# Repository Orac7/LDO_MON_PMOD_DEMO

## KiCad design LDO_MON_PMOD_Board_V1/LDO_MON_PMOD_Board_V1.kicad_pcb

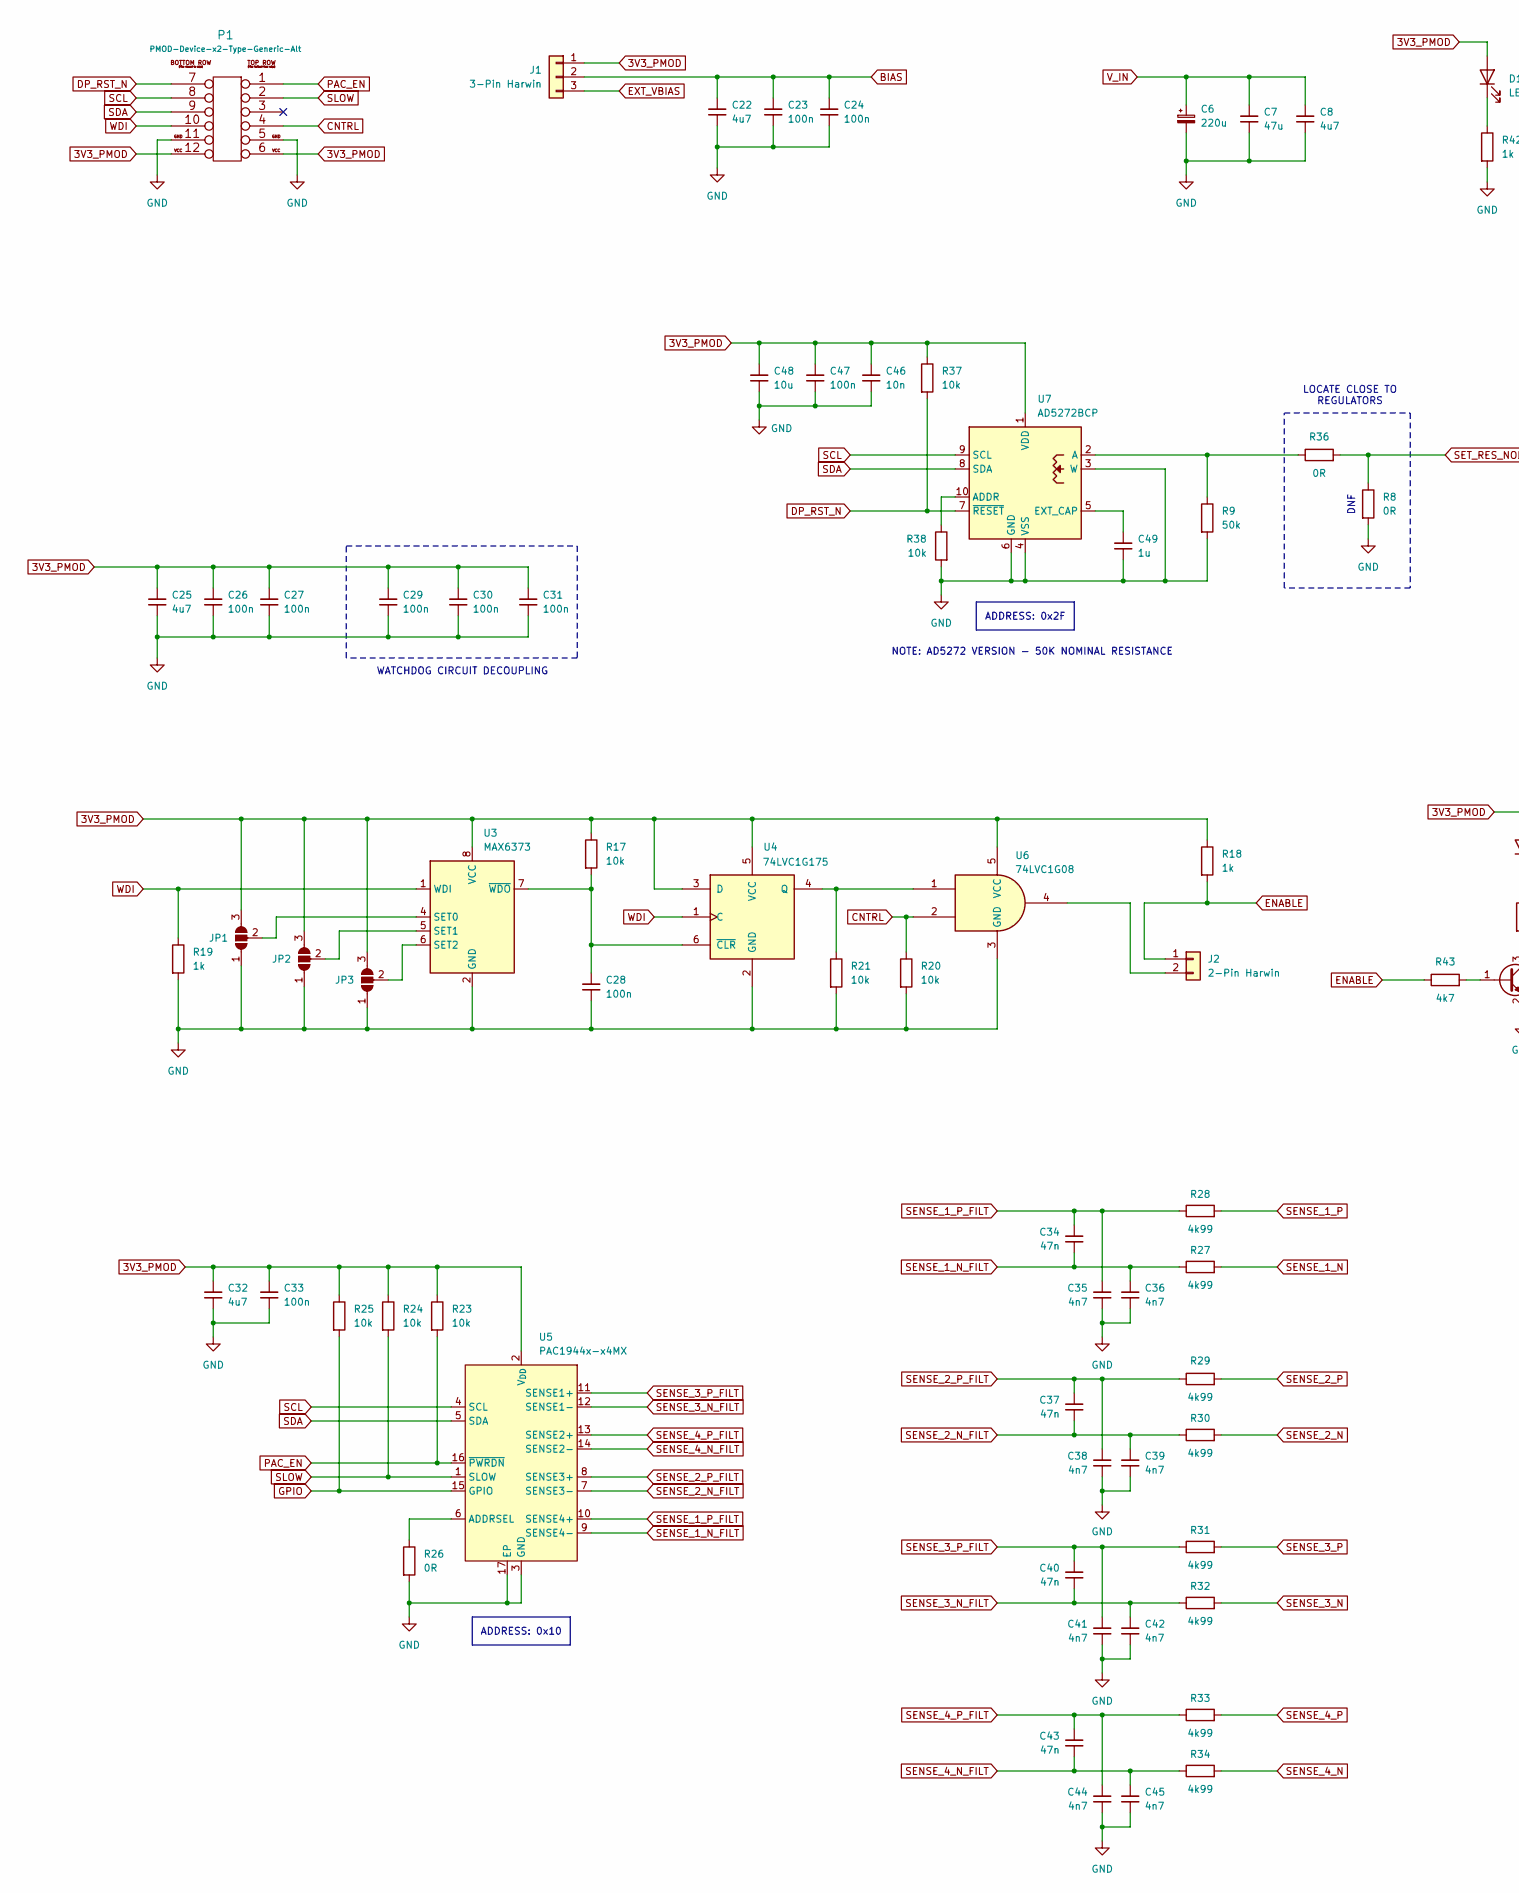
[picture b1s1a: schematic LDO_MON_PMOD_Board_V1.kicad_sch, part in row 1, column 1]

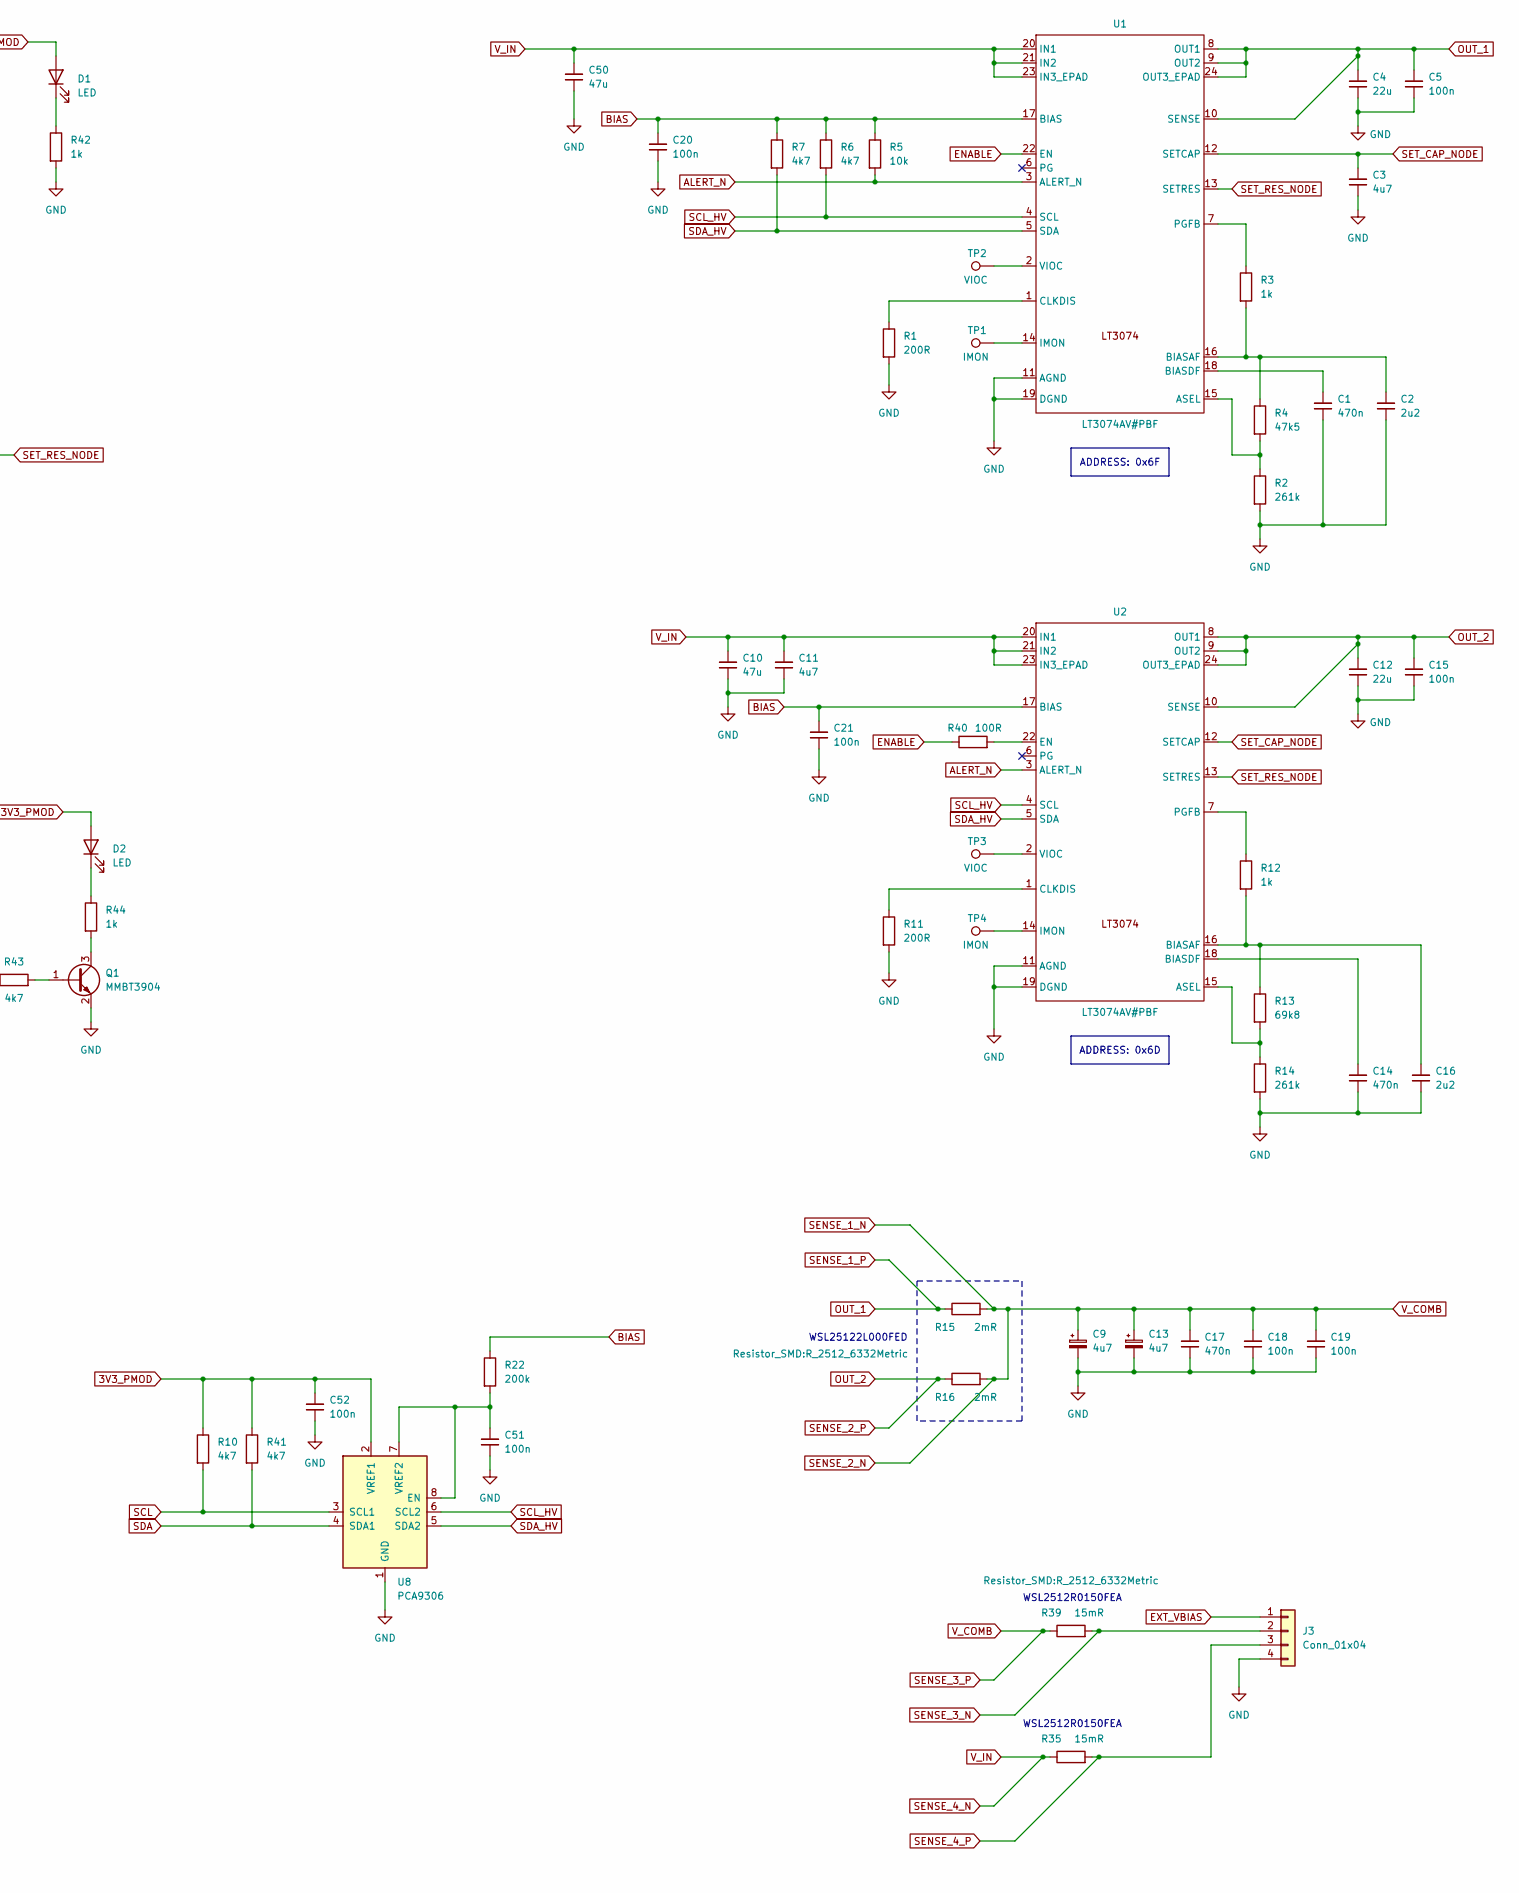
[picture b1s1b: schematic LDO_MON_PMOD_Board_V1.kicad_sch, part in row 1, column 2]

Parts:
C1, C14, C17: 470n; C_0402_1005Metric
C2, C16: 2u2; C_0603_1608Metric
C3, C8, C9, C11, C13, C22, C25, C32: 4u7; C_0603_1608Metric
C4, C12: 22u; C_1210_3225Metric
C5, C15, C18, C19, C20, C21, C23, C24, C26, C27, C28, C29, C30, C31, C33, C47, C51, C52: 100n; C_0402_1005Metric
C6: 220u; CP_Elec_8x10
C7, C10, C50: 47u; C_1210_3225Metric
C34, C37, C40, C43: 47n; C_0402_1005Metric
C35, C36, C38, C39, C41, C42, C44, C45: 4n7; C_0402_1005Metric
C46: 10n; C_0402_1005Metric
C48: 10u; C_0603_1608Metric
C49: 1u; C_0402_1005Metric
D1, D2: LED; LED_0402_1005Metric
J1: 3-Pin Harwin; PinHeader_1x03_P2.54mm_Vertical
J2: 2-Pin Harwin; PinHeader_1x02_P2.54mm_Vertical
J3: Conn_01x04; PhoenixContact_MC_1,5_4-G-3.5_1x04_P3.50mm_Horizontal
JP1, JP2, JP3: SolderJumper_3_Open; SolderJumper-3_P1.3mm_Open_RoundedPad1.0x1.5mm
P1: PMOD-Device-x2-Type-Generic-Alt; pmod_pin_array_6x2
Q1: MMBT3904; SOT-23
R1, R11: 200R; R_0402_1005Metric
R2, R14: 261k; R_0402_1005Metric
R3, R12, R18, R19, R42, R44: 1k; R_0402_1005Metric
R4: 47k5; R_0402_1005Metric
R5, R17, R20, R21, R23, R24, R25, R37, R38: 10k; R_0402_1005Metric
R6, R7, R10, R41, R43: 4k7; R_0402_1005Metric
R8, R26, R36: 0R; R_0402_1005Metric
R9: 50k; R_0402_1005Metric
R13: 69k8; R_0402_1005Metric
R15, R16: 2mR; R_2512_6332Metric
R22: 200k; R_0402_1005Metric
R27, R28, R29, R30, R31, R32, R33, R34: 4k99; R_0402_1005Metric
R35, R39: 15mR; R_2512_6332Metric
R40: 100R; R_0402_1005Metric
TP1, TP4: IMON; TestPoint_Pad_1.0x1.0mm
TP2, TP3: VIOC; TestPoint_Pad_1.0x1.0mm
U1, U2: LT3074AV#PBF
U3: MAX6373; SOT-23-8
U4: 74LVC1G175; SOT-23-6
U5: PAC1944x-x4MX; VQFN-16-1EP_3x3mm_P0.5mm_EP1.1x1.1mm
U6: 74LVC1G08; Texas_R-PDSO-N5_DRL-5
U7: AD5272BCP; LFCSP-WD-10-1EP_3x3mm_P0.5mm_EP1.64x2.38mm
U8: PCA9306; VSSOP-8_2.3x2mm_P0.5mm

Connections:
3V3_PMOD: C25.1, C26.1, C27.1, C29.1, C30.1, C31.1, C32.1, C33.1, C46.1, C47.1, C48.1, C52.1, D1.2 (A), D2.2 (A), J1.1, JP1.3 (B), JP2.3 (B), JP3.3 (B), P1.6, P1.12, R10.1, R17.1, R18.1, R23.1, R24.1, R25.1, R37.1, R41.1, U3.8 (VCC), U4.3 (D), U4.5 (VCC), U5.2 (V_{DD}), U6.5 (VCC), U7.1 (VDD), U8.2 (VREF1)
ALERT_N: R5.2, U1.3 (ALERT_N), U2.3 (ALERT_N)
BIAS: C20.1, C21.1, C22.1, C23.1, C24.1, J1.2, R5.1, R6.1, R7.1, R22.1, U1.17 (BIAS), U2.17 (BIAS)
CNTRL: P1.4, R20.1, U6.2
DP_RST_N: P1.7, R37.2, U7.7 (~RESET)
ENABLE: J2.1, R18.2, R40.1, R43.1, U1.22 (EN)
EXT_VBIAS: J1.3, J3.1
GND: C1.2, C2.2, C3.2, C4.2, C5.2, C6.2, C7.2, C8.2, C9.2, C10.2, C11.2, C12.2, C13.2, C14.2, C15.2, C16.2, C17.2, C18.2, C19.2, C20.2, C21.2, C22.2, C23.2, C24.2, C25.2, C26.2, C27.2, C28.2, C29.2, C30.2, C31.2, C32.2, C33.2, C35.2, C36.2, C38.2, C39.2, C41.2, C42.2, C44.2, C45.2, C46.2, C47.2, C48.2, C49.2, C50.2, C51.2, C52.2, J3.4, JP1.1 (A), JP2.1 (A), JP3.1 (A), P1.5, P1.11, Q1.2 (E), R1.2, R2.2, R8.2, R9.2, R11.2, R14.2, R19.2, R20.2, R21.2, R26.2, R38.2, R42.2, U1.11 (AGND), U1.19 (DGND), U2.11 (AGND), U2.19 (DGND), U3.2 (GND), U4.2 (GND), U5.3 (GND), U5.17 (EP), U6.3 (GND), U7.3 (W), U7.4 (VSS), U7.6 (GND), U7.11 (VSS), U8.1 (GND)
GPIO: R25.2, U5.15 (GPIO)
unnamed: D1.1 (K), R42.1
unnamed: D2.1 (K), R44.1
unnamed: J2.2, U6.4
unnamed: JP1.2 (C), U3.4 (SET0)
unnamed: JP2.2 (C), U3.5 (SET1)
unnamed: JP3.2 (C), U3.6 (SET2)
unnamed: Q1.1 (B), R43.2
unnamed: Q1.3 (C), R44.2
unnamed: R2.1, R4.2, U1.15 (ASEL)
unnamed: C2.1, R3.2, R4.1, U1.16 (BIASAF)
unnamed: C1.1, U1.18 (BIASDF)
unnamed: R1.1, U1.1 (CLKDIS)
unnamed: TP1.1 (1_1), U1.14 (IMON)
unnamed: R3.1, U1.7 (PGFB)
unnamed: TP2.1 (1_1), U1.2 (VIOC)
unnamed: R13.2, R14.1, U2.15 (ASEL)
unnamed: C16.1, R12.2, R13.1, U2.16 (BIASAF)
unnamed: C14.1, U2.18 (BIASDF)
unnamed: R11.1, U2.1 (CLKDIS)
unnamed: R40.2, U2.22 (EN)
unnamed: TP4.1 (1_1), U2.14 (IMON)
unnamed: R12.1, U2.7 (PGFB)
unnamed: TP3.1 (1_1), U2.2 (VIOC)
unnamed: C28.1, R17.2, U3.7 (~WDO), U4.6 (~CLR)
unnamed: R21.1, U4.4 (Q), U6.1
unnamed: R26.1, U5.6 (ADDRSEL)
unnamed: R9.1, R36.1, U7.2 (A)
unnamed: R38.1, U7.10 (ADDR)
unnamed: C49.1, U7.5 (EXT_CAP)
unnamed: C51.1, R22.2, U8.7 (VREF2), U8.8 (EN)
OUT_1: C4.1, C5.1, R15.1, R28.2, U1.8 (OUT1), U1.9 (OUT2), U1.10 (SENSE), U1.24 (OUT3_EPAD)
OUT_2: C12.1, C15.1, R16.1, R29.2, U2.8 (OUT1), U2.9 (OUT2), U2.10 (SENSE), U2.24 (OUT3_EPAD)
PAC_EN: P1.1, R23.2, U5.16 (~PWRDN)
SCL: P1.8, R10.2, U5.4 (SCL), U7.9 (SCL), U8.3 (SCL1)
SCL_HV: R6.2, U1.4 (SCL), U2.4 (SCL), U8.6 (SCL2)
SDA: P1.9, R41.2, U5.5 (SDA), U7.8 (SDA), U8.4 (SDA1)
SDA_HV: R7.2, U1.5 (SDA), U2.5 (SDA), U8.5 (SDA2)
SENSE_1_N: C9.1, C13.1, C17.1, C18.1, C19.1, R15.2, R16.2, R27.2, R30.2, R31.2, R39.1
SENSE_1_N_FILT: C34.2, C36.1, R27.1, U5.9 (SENSE4-)
SENSE_1_P_FILT: C34.1, C35.1, R28.1, U5.10 (SENSE4+)
SENSE_2_N_FILT: C37.2, C39.1, R30.1, U5.7 (SENSE3-)
SENSE_2_P_FILT: C37.1, C38.1, R29.1, U5.8 (SENSE3+)
SENSE_3_N: J3.2, R32.2, R39.2
SENSE_3_N_FILT: C40.2, C42.1, R32.1, U5.12 (SENSE1-)
SENSE_3_P_FILT: C40.1, C41.1, R31.1, U5.11 (SENSE1+)
SENSE_4_N: C6.1, C7.1, C8.1, C10.1, C11.1, C50.1, R34.2, R35.1, U1.20 (IN1), U1.21 (IN2), U1.23 (IN3_EPAD), U2.20 (IN1), U2.21 (IN2), U2.23 (IN3_EPAD)
SENSE_4_N_FILT: C43.2, C45.1, R34.1, U5.14 (SENSE2-)
SENSE_4_P: J3.3, R33.2, R35.2
SENSE_4_P_FILT: C43.1, C44.1, R33.1, U5.13 (SENSE2+)
SET_CAP_NODE: C3.1, U1.12 (SETCAP), U2.12 (SETCAP)
SET_RES_NODE: R8.1, R36.2, U1.13 (SETRES), U2.13 (SETRES)
SLOW: P1.2, R24.2, U5.1 (SLOW)
WDI: P1.10, R19.1, U3.1 (WDI), U4.1 (C)

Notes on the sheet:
ADDRESS: 0x6D
NOTE: AD5272 VERSION - 50K NOMINAL RESISTANCE
ADDRESS: 0x6F
ADDRESS: 0x2F
WATCHDOG CIRCUIT DECOUPLING
WSL2512R0150FEA
ADDRESS: 0x10
WSL25122L000FED
LOCATE CLOSE TO REGULATORS
DNF

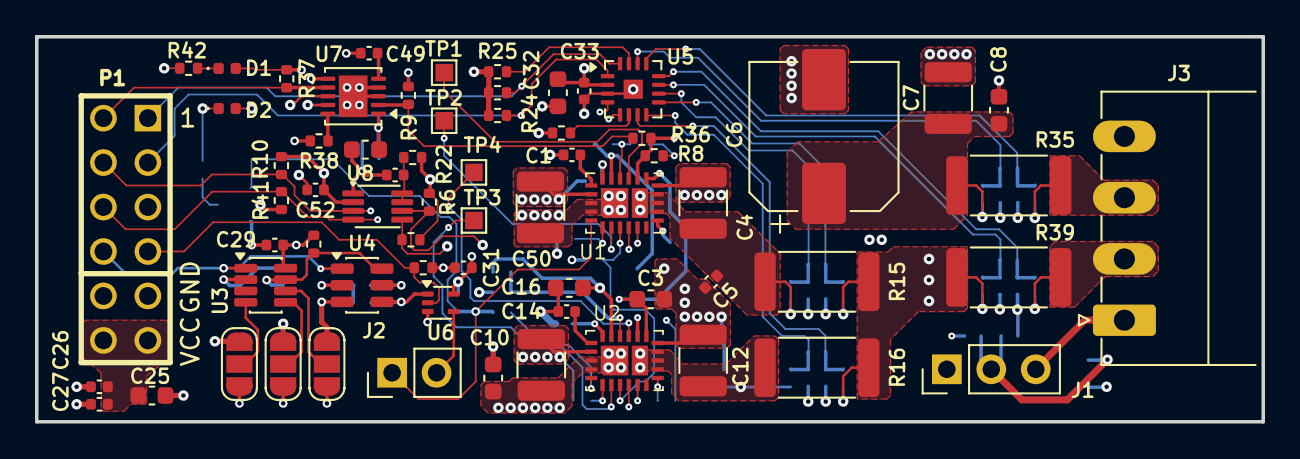
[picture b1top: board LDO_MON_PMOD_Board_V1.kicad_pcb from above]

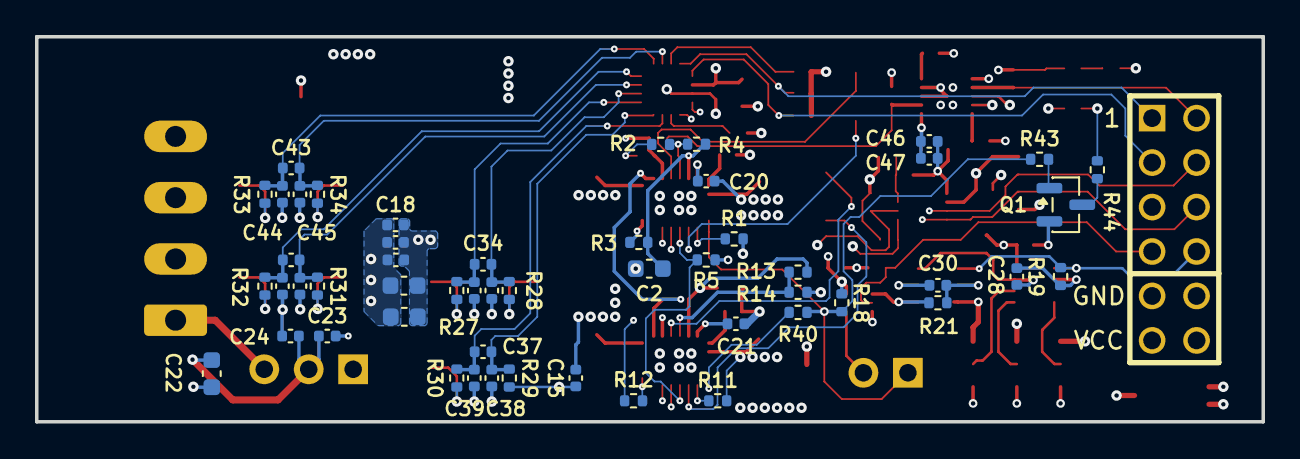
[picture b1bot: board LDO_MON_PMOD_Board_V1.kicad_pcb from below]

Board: 6 copper layers, 70.1 x 22.0 mm, 118 parts (52 on the bottom side), 62 nets.

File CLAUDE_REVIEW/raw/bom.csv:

"Refs","Value","Footprint","Qty","DNP"
"C1","470n","Capacitor_SMD:C_0402_1005Metric","1",""
"C2","2u2","Capacitor_SMD:C_0603_1608Metric","1",""
"C3","4u7","Capacitor_SMD:C_0603_1608Metric","1",""
"C4","22u","Capacitor_SMD:C_1210_3225Metric","1",""
"C5","100n","Capacitor_SMD:C_0402_1005Metric","1",""
"C6","220u","Capacitor_SMD:CP_Elec_8x10","1",""
"C7","47u","Capacitor_SMD:C_1210_3225Metric","1",""
"C8","4u7","Capacitor_SMD:C_0603_1608Metric","1",""
"C9","4u7","Capacitor_SMD:C_0603_1608Metric","1",""
"C10","47u","Capacitor_SMD:C_1210_3225Metric","1",""
"C11","4u7","Capacitor_SMD:C_0603_1608Metric","1",""
"C12","22u","Capacitor_SMD:C_1210_3225Metric","1",""
"C13","4u7","Capacitor_SMD:C_0603_1608Metric","1",""
"C14","470n","Capacitor_SMD:C_0402_1005Metric","1",""
"C15","100n","Capacitor_SMD:C_0402_1005Metric","1",""
"C16","2u2","Capacitor_SMD:C_0603_1608Metric","1",""
"C17","470n","Capacitor_SMD:C_0402_1005Metric","1",""
"C18","100n","Capacitor_SMD:C_0402_1005Metric","1",""
"C19","100n","Capacitor_SMD:C_0402_1005Metric","1",""
"C20","100n","Capacitor_SMD:C_0402_1005Metric","1",""
"C21","100n","Capacitor_SMD:C_0402_1005Metric","1",""
"C22","4u7","Capacitor_SMD:C_0603_1608Metric","1",""
"C23","100n","Capacitor_SMD:C_0402_1005Metric","1",""
"C24","100n","Capacitor_SMD:C_0402_1005Metric","1",""
"C25","4u7","Capacitor_SMD:C_0603_1608Metric","1",""
"C26","100n","Capacitor_SMD:C_0402_1005Metric","1",""
"C27","100n","Capacitor_SMD:C_0402_1005Metric","1",""
"C28","100n","Capacitor_SMD:C_0402_1005Metric","1",""
"C29","100n","Capacitor_SMD:C_0402_1005Metric","1",""
"C30","100n","Capacitor_SMD:C_0402_1005Metric","1",""
"C31","100n","Capacitor_SMD:C_0402_1005Metric","1",""
"C32","4u7","Capacitor_SMD:C_0603_1608Metric","1",""
"C33","100n","Capacitor_SMD:C_0402_1005Metric","1",""
"C34","47n","Capacitor_SMD:C_0402_1005Metric","1",""
"C35","4n7","Capacitor_SMD:C_0402_1005Metric","1",""
"C36","4n7","Capacitor_SMD:C_0402_1005Metric","1",""
"C37","47n","Capacitor_SMD:C_0402_1005Metric","1",""
"C38","4n7","Capacitor_SMD:C_0402_1005Metric","1",""
"C39","4n7","Capacitor_SMD:C_0402_1005Metric","1",""
"C40","47n","Capacitor_SMD:C_0402_1005Metric","1",""
"C41","4n7","Capacitor_SMD:C_0402_1005Metric","1",""
"C42","4n7","Capacitor_SMD:C_0402_1005Metric","1",""
"C43","47n","Capacitor_SMD:C_0402_1005Metric","1",""
"C44","4n7","Capacitor_SMD:C_0402_1005Metric","1",""
"C45","4n7","Capacitor_SMD:C_0402_1005Metric","1",""
"C46","10n","Capacitor_SMD:C_0402_1005Metric","1",""
"C47","100n","Capacitor_SMD:C_0402_1005Metric","1",""
"C48","10u","Capacitor_SMD:C_0603_1608Metric","1",""
"C49","1u","Capacitor_SMD:C_0402_1005Metric","1",""
"C50","47u","Capacitor_SMD:C_1210_3225Metric","1",""
"C51","100n","Capacitor_SMD:C_0402_1005Metric","1",""
"C52","100n","Capacitor_SMD:C_0402_1005Metric","1",""
"D1","LED","LED_SMD:LED_0402_1005Metric","1",""
"D2","LED","LED_SMD:LED_0402_1005Metric","1",""
"J1","3-Pin Harwin","Connector_PinHeader_2.54mm:PinHeader_1x03_P2.54mm_Vertical","1",""
"J2","2-Pin Harwin","Connector_PinHeader_2.54mm:PinHeader_1x02_P2.54mm_Vertical","1",""
"J3","Conn_01x04","Connector_Phoenix_MC:PhoenixContact_MC_1,5_4-G-3.5_1x04_P3.50mm_Horizontal","1",""
"P1","PMOD-Device-x2-Type-Generic-Alt","klib_connectors:pmod_pin_array_6x2","1",""
"Q1","MMBT3904","Package_TO_SOT_SMD:SOT-23","1",""
"R1","200R","Resistor_SMD:R_0402_1005Metric","1",""
"R2","261k","Resistor_SMD:R_0402_1005Metric","1",""
"R3","1k","Resistor_SMD:R_0402_1005Metric","1",""
"R4","47k5","Resistor_SMD:R_0402_1005Metric","1",""
"R5","10k","Resistor_SMD:R_0402_1005Metric","1",""
"R6","4k7","Resistor_SMD:R_0402_1005Metric","1",""
"R7","4k7","Resistor_SMD:R_0402_1005Metric","1",""
"R8","0R","Resistor_SMD:R_0402_1005Metric","1",""
"R9","50k","Resistor_SMD:R_0402_1005Metric","1",""
"R10","4k7","Resistor_SMD:R_0402_1005Metric","1",""
"R11","200R","Resistor_SMD:R_0402_1005Metric","1",""
"R12","1k","Resistor_SMD:R_0402_1005Metric","1",""
"R13","69k8","Resistor_SMD:R_0402_1005Metric","1",""
"R14","261k","Resistor_SMD:R_0402_1005Metric","1",""
"R15","2mR","Resistor_SMD:R_2512_6332Metric","1",""
"R16","2mR","Resistor_SMD:R_2512_6332Metric","1",""
"R17","10k","Resistor_SMD:R_0402_1005Metric","1",""
"R18","1k","Resistor_SMD:R_0402_1005Metric","1",""
"R19","1k","Resistor_SMD:R_0402_1005Metric","1",""
"R20","10k","Resistor_SMD:R_0402_1005Metric","1",""
"R21","10k","Resistor_SMD:R_0402_1005Metric","1",""
"R22","200k","Resistor_SMD:R_0402_1005Metric","1",""
"R23","10k","Resistor_SMD:R_0402_1005Metric","1",""
"R24","10k","Resistor_SMD:R_0402_1005Metric","1",""
"R25","10k","Resistor_SMD:R_0402_1005Metric","1",""
"R26","0R","Resistor_SMD:R_0402_1005Metric","1",""
"R27","4k99","Resistor_SMD:R_0402_1005Metric","1",""
"R28","4k99","Resistor_SMD:R_0402_1005Metric","1",""
"R29","4k99","Resistor_SMD:R_0402_1005Metric","1",""
"R30","4k99","Resistor_SMD:R_0402_1005Metric","1",""
"R31","4k99","Resistor_SMD:R_0402_1005Metric","1",""
"R32","4k99","Resistor_SMD:R_0402_1005Metric","1",""
"R33","4k99","Resistor_SMD:R_0402_1005Metric","1",""
"R34","4k99","Resistor_SMD:R_0402_1005Metric","1",""
"R35","15mR","Resistor_SMD:R_2512_6332Metric","1",""
"R36","0R","Resistor_SMD:R_0402_1005Metric","1",""
"R37","10k","Resistor_SMD:R_0402_1005Metric","1",""
"R38","10k","Resistor_SMD:R_0402_1005Metric","1",""
"R39","15mR","Resistor_SMD:R_2512_6332Metric","1",""
"R40","100R","Resistor_SMD:R_0402_1005Metric","1",""
"R41","4k7","Resistor_SMD:R_0402_1005Metric","1",""
"R42","1k","Resistor_SMD:R_0402_1005Metric","1",""
"R43","4k7","Resistor_SMD:R_0402_1005Metric","1",""
"R44","1k","Resistor_SMD:R_0402_1005Metric","1",""
"TP1","IMON","TestPoint:TestPoint_Pad_1.0x1.0mm","1",""
"TP2","VIOC","TestPoint:TestPoint_Pad_1.0x1.0mm","1",""
"TP3","VIOC","TestPoint:TestPoint_Pad_1.0x1.0mm","1",""
"TP4","IMON","TestPoint:TestPoint_Pad_1.0x1.0mm","1",""
"U1","LT3074AV#PBF","klib_logic:LT3074AV#PBF","1",""
"U2","LT3074AV#PBF","klib_logic:LT3074AV#PBF","1",""
"U3","MAX6373","Package_TO_SOT_SMD:SOT-23-8","1",""
"U4","74LVC1G175","Package_TO_SOT_SMD:SOT-23-6","1",""
"U5","PAC1944x-x4MX","Package_DFN_QFN:VQFN-16-1EP_3x3mm_P0.5mm_EP1.1x1.1mm","1",""
"U6","74LVC1G08","Package_TO_SOT_SMD:Texas_R-PDSO-N5_DRL-5","1",""
"U7","AD5272BCP","Package_CSP:LFCSP-WD-10-1EP_3x3mm_P0.5mm_EP1.64x2.38mm","1",""
"U8","PCA9306","Package_SO:VSSOP-8_2.3x2mm_P0.5mm","1",""
